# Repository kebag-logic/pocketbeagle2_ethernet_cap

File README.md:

# PocketBeagle 2 Ethernet Cap

Ethernet cap for the PocketBeagle 2, exposing the TSN features of the AM62x through a
DP83867IRPAPR gigabit PHY (RGMII), with full IO pass-through headers for stacking additional modules.

## Getting started

```sh
git clone <this repo>
git submodule update --init     # pulls kebag_logic_kicad_library
```

Open `pocketbeagle2_ethernet_cap.kicad_pro` with KiCad ≥ 9. All symbols/footprints
resolve project-locally through `sym-lib-table` / `fp-lib-table` into the
[kebag_logic_kicad_library](https://github.com/kebag-logic/kebag_logic_kicad_library)
submodule — no global library setup needed.

## Schematic structure

```
pocketbeagle2_ethernet_cap.kicad_sch   root: pure block diagram (sheet symbols only)
├── io.kicad_sch                       U1 PocketBeagle 2 + J2/J3 IO pass-through headers
├── network.kicad_sch                  network domain top
│   ├── phy.kicad_sch                  U2 DP83867 PHY, straps, decoupling, status LEDs
│   ├── rj45_connector_port0.kicad_sch J1 RJ45 magjack (integrated magnetics)
│   └── oscillator.kicad_sch           Y1 25 MHz HCMOS oscillator + clock conditioning
├── ldo_2v5.kicad_sch                  U4 TPS7A2025 -> VDD_2V5
└── ldo_1v1.kicad_sch                  U3 TPS7A2011 -> VDD_1V1
```

The design is fully hierarchical (shish-lan house style): **no global labels**. `GND`
is distributed via `power:GND` symbols; every other inter-sheet net crosses through
**hierarchical sheet-pin ports**, so signal flow is traceable through the hierarchy.
The root is a block diagram: `io` sources the RGMII/MDIO/reset/interrupt signals and
`VDD_3V3`, `network` consumes them, and the `ldo_*` sheets feed `VDD_2V5`/`VDD_1V1`.
Inside `io`, the PocketBeagle IOs fan out to the stacking headers as sheet-local nets;
only the 17 cap-used signals leave the sheet as ports.

## Documentation

- [documentation/connections.md](documentation/connections.md) — RGMII, MDI, MDIO,
  clocking, straps, audio, power tree, and the rev A → current net rename map
- [documentation/naming_convention.md](documentation/naming_convention.md) — mandatory
  signal naming rules
- [documentation/review_checklist.md](documentation/review_checklist.md) — everything
  awaiting user review after the restructure
- [documentation/library_additions.md](documentation/library_additions.md) — every
  part added to the KL library for this design (review checkpoint)
- [documentation/U2-DP83867IRPAPR_pin_out.md](documentation/U2-DP83867IRPAPR_pin_out.md)
- [documentation/current_consumption.md](documentation/current_consumption.md)

## Board state

**Rev B** (branch `revb-respin`) is manufactured and assembled by JLCPCB. All SMD parts are on the
top side; the RJ45 magjack J1 (TE 5-2301994-7, pin 1 left unsoldered) is hand-soldered on the bottom
and runs through the DP83867 RJ45 mirror mode. RGMII lengths are matched including the PocketBeagle 2
module side. Design and order details: [documentation/handover_revb_respin.md](documentation/handover_revb_respin.md).

Bring-up status (2026-10-07):

| Step | Result |
|------|--------|
| Visual inspection, rail-to-GND shorts | OK |
| Bench 3.3 V on P1.14, cape alone: VDD_2V5 / VDD_1V1 | OK |
| PocketBeagle 2 on USB-C, no SD card: rails | OK |
| Ethernet link LED on cable plug/unplug (PHY out of reset, auto-negotiation) | OK |
| Link speed on the switch side: 1000 Mb/s (all 4 pairs and mirror mode work) | OK |
| Linux: PHY detected over MDIO, 1000/Full, iperf3, RGMII delay tuning | to do (needs SD card) |

### Software

A Linux image for the PocketBeagle 2 with this cape is built from the
[ti-sitara-am65x-bsp](https://github.com/kebag-logic/ti-sitara-am65x-bsp). The device tree needs the PHY at `reg = <0>` and
`phy-mode = "rgmii-rxid"` (start with a 1.75 ns RX delay); see section 2.4 of the handover.

### Rev B pictures

Assembled board on the PocketBeagle 2:

Layout and 3D views:

### Rev A

The **rev A** routed board is preserved at git tag `revA-routed` (flight-time matching on the RGMII was
still open there).

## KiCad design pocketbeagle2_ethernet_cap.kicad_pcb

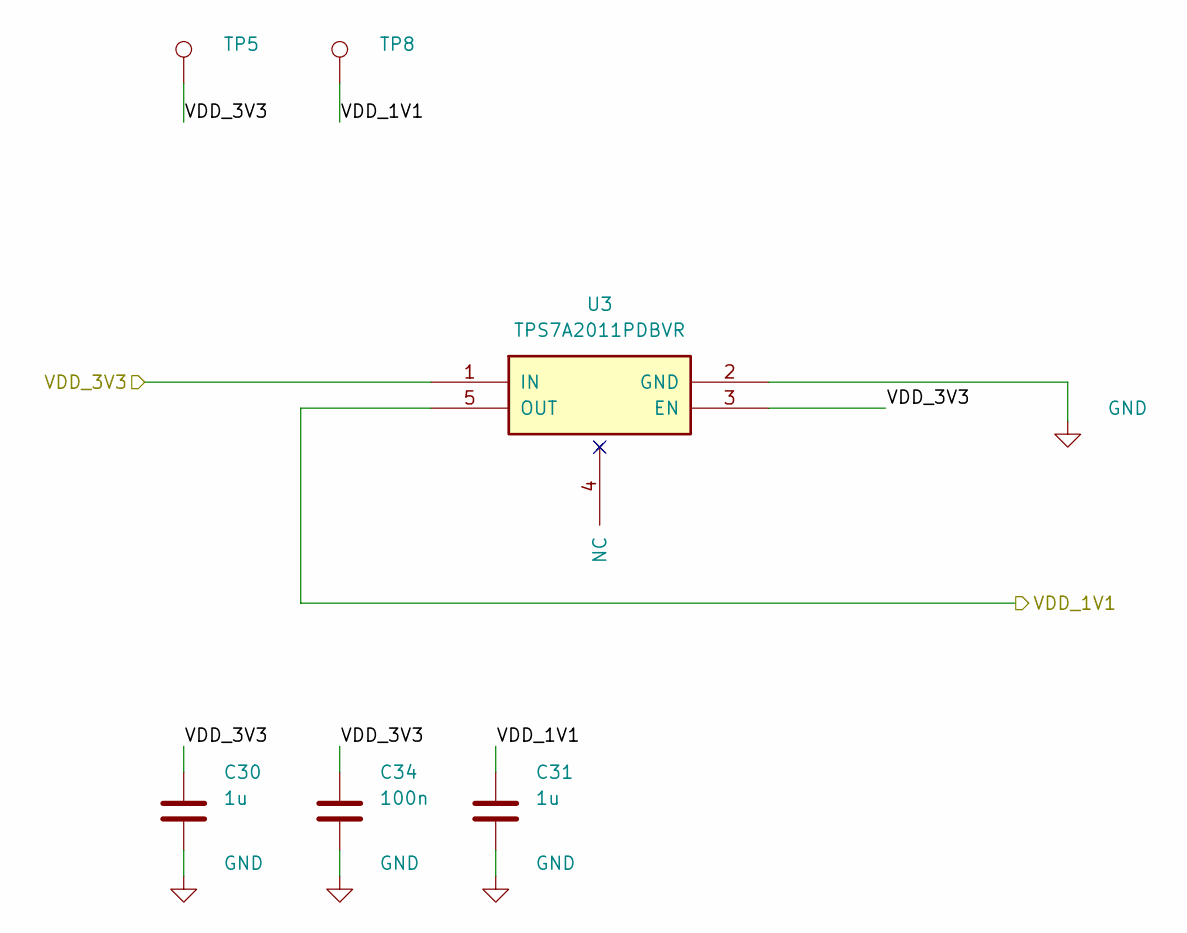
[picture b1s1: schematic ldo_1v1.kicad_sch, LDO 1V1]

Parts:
C30, C31: 1u; C_0402; Voltage_in_V 16; Tolerance_in_pct 10; MPN GRM155R61C105KA12D; Mouser 81-GRM155R61C105KA12D
C34: 100n; C_0402; Voltage_in_V 35; Tolerance_in_pct 10; MPN CGA2B3X7R1V104K050BB; Mouser 810-CGA2B3X7R1V104K
TP5, TP8: TestPoint_SMD; TestPoint_SMD_1.0x1.0mm
U3: TPS7A2011PDBVR; SOT-23-5; MPN TPS7A2011PDBVR; Mouser 595-TPS7A2011PDBVR

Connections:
/VDD_1V1: C31.1, TP8.1, U3.5 (OUT); also elsewhere on the board
/VDD_3V3: C30.1, C34.1, TP5.1, U3.1 (IN), U3.3 (EN); also elsewhere on the board
GND: C30.2, C31.2, C34.2, U3.2 (GND); also elsewhere on the board

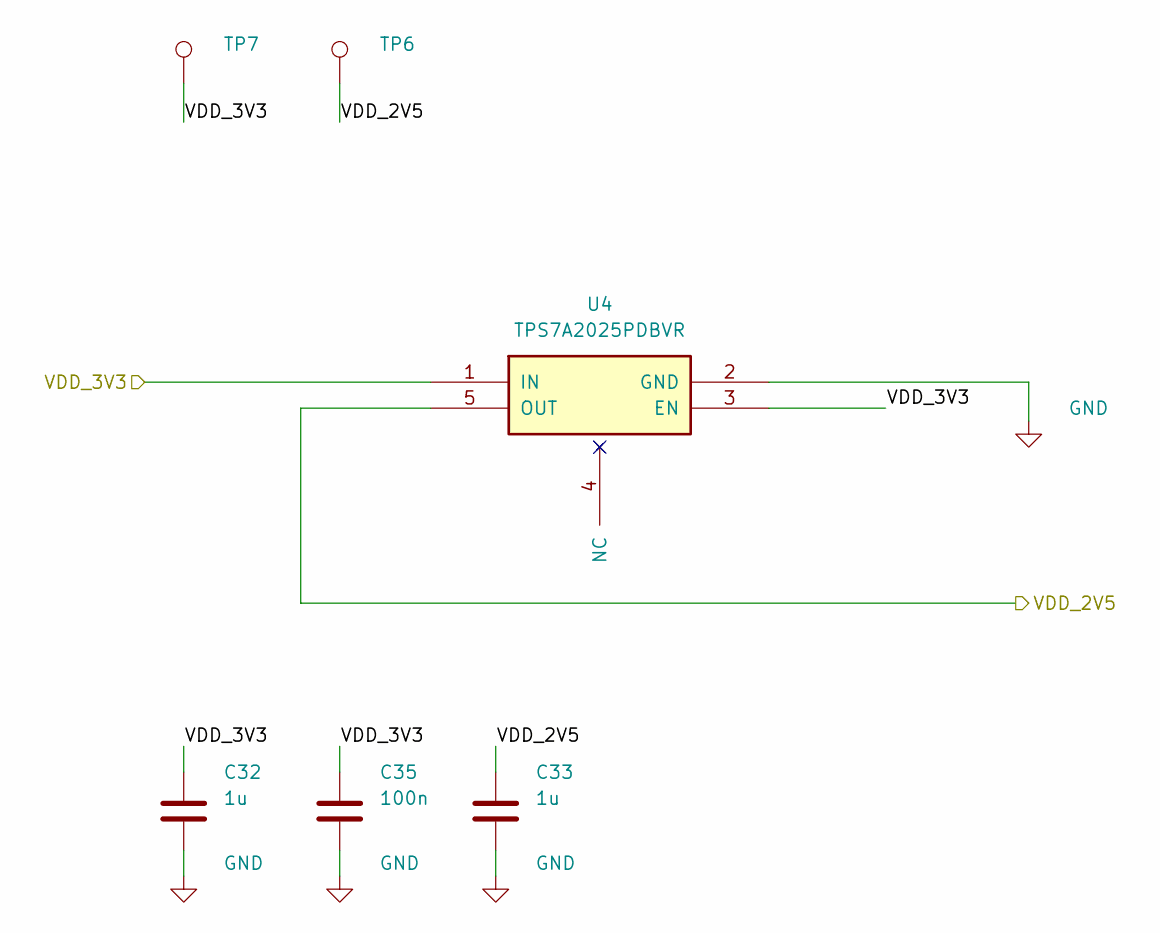
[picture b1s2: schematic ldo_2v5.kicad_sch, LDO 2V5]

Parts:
C32, C33: 1u; C_0402; Voltage_in_V 16; Tolerance_in_pct 10; MPN GRM155R61C105KA12D; Mouser 81-GRM155R61C105KA12D
C35: 100n; C_0402; Voltage_in_V 35; Tolerance_in_pct 10; MPN CGA2B3X7R1V104K050BB; Mouser 810-CGA2B3X7R1V104K
TP6, TP7: TestPoint_SMD; TestPoint_SMD_1.0x1.0mm
U4: TPS7A2025PDBVR; SOT-23-5; MPN TPS7A2025PDBVR; Mouser 595-TPS7A2025PDBVR

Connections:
/VDD_2V5: C33.1, TP6.1, U4.5 (OUT); also elsewhere on the board
/VDD_3V3: C32.1, C35.1, TP7.1, U4.1 (IN), U4.3 (EN); also elsewhere on the board
GND: C32.2, C33.2, C35.2, U4.2 (GND); also elsewhere on the board

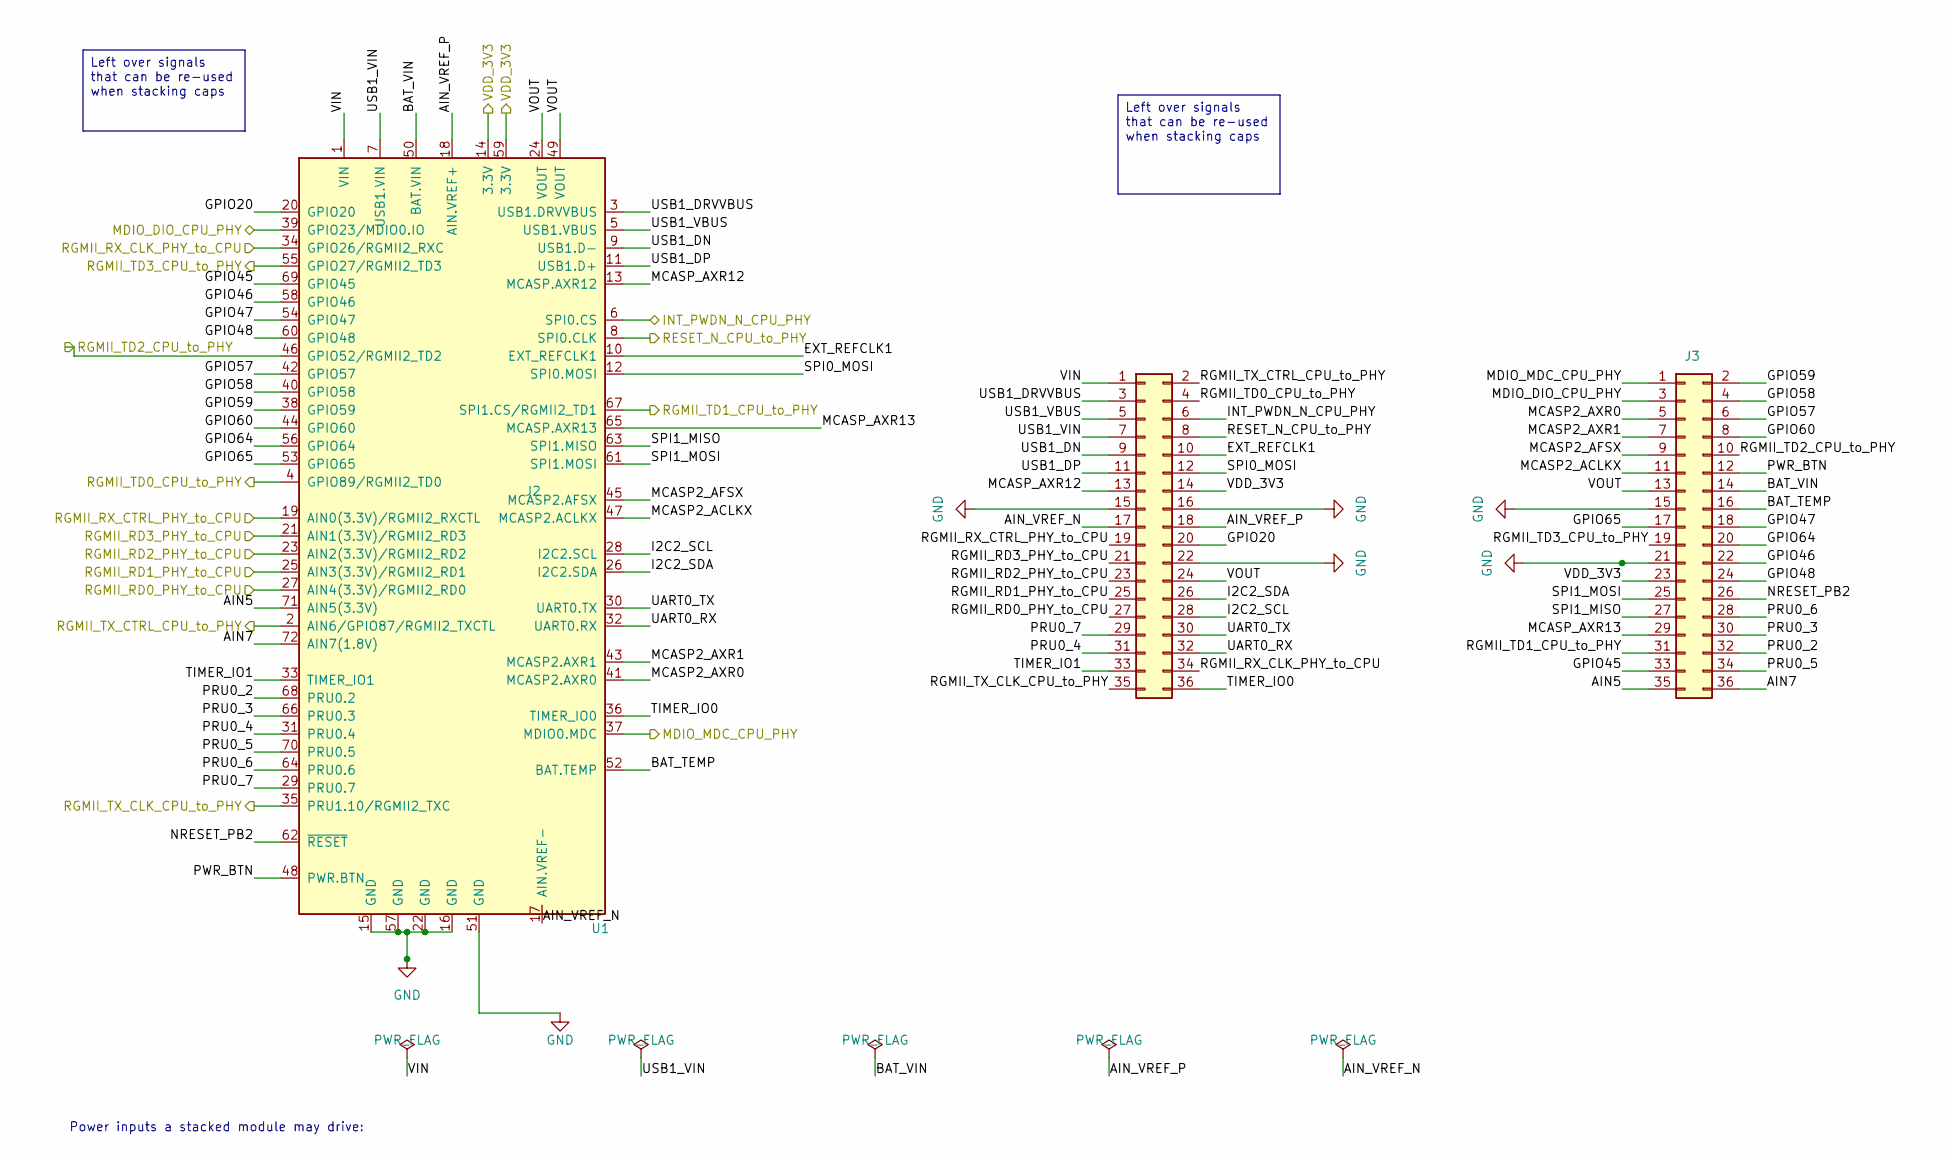
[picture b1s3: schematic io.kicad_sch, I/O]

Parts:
J2, J3: Header_18x02_2.54mm_2.54mm_Straight; 18x02_2.54mm_Header; MPN HC-PZ254-11.5L-2x18PZ; LCSC C41376109
U1: PocketBeagle2; BeagleBoard_PocketBeagle; MPN PocketBeagle 2; Mouser TBD

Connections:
/INT_PWDN_N_CPU_PHY: J2.6, U1.6 (SPI0.CS); also elsewhere on the board
/MDIO_DIO_CPU_PHY: J3.3, U1.39 (GPIO23/MDIO0.IO); also elsewhere on the board
/MDIO_MDC_CPU_PHY: J3.1, U1.37 (MDIO0.MDC); also elsewhere on the board
/RESET_N_CPU_to_PHY: J2.8, U1.8 (SPI0.CLK); also elsewhere on the board
/RGMII_RD0_PHY_to_CPU: J2.27, U1.27 (AIN4(3.3V)/RGMII2_RD0); also elsewhere on the board
/RGMII_RD1_PHY_to_CPU: J2.25, U1.25 (AIN3(3.3V)/RGMII2_RD1); also elsewhere on the board
/RGMII_RD2_PHY_to_CPU: J2.23, U1.23 (AIN2(3.3V)/RGMII2_RD2); also elsewhere on the board
/RGMII_RD3_PHY_to_CPU: J2.21, U1.21 (AIN1(3.3V)/RGMII2_RD3); also elsewhere on the board
/RGMII_RX_CLK_PHY_to_CPU: J2.34, U1.34 (GPIO26/RGMII2_RXC); also elsewhere on the board
/RGMII_RX_CTRL_PHY_to_CPU: J2.19, U1.19 (AIN0(3.3V)/RGMII2_RXCTL); also elsewhere on the board
/RGMII_TD0_CPU_to_PHY: J2.4, U1.4 (GPIO89/RGMII2_TD0); also elsewhere on the board
/RGMII_TD1_CPU_to_PHY: J3.31, U1.67 (SPI1.CS/RGMII2_TD1); also elsewhere on the board
/RGMII_TD2_CPU_to_PHY: J3.10, U1.46 (GPIO52/RGMII2_TD2); also elsewhere on the board
/RGMII_TD3_CPU_to_PHY: J3.19, U1.55 (GPIO27/RGMII2_TD3); also elsewhere on the board
/RGMII_TX_CLK_CPU_to_PHY: J2.35, U1.35 (PRU1.10/RGMII2_TXC); also elsewhere on the board
/RGMII_TX_CTRL_CPU_to_PHY: J2.2, U1.2 (AIN6/GPIO87/RGMII2_TXCTL); also elsewhere on the board
/VDD_3V3: J2.14, J3.23, U1.14 (3.3V), U1.59 (3.3V); also elsewhere on the board
/io/AIN5: J3.35, U1.71 (AIN5(3.3V))
/io/AIN7: J3.36, U1.72 (AIN7(1.8V))
/io/AIN_VREF_N: J2.17, U1.17 (AIN.VREF-)
/io/AIN_VREF_P: J2.18, U1.18 (AIN.VREF+)
/io/BAT_TEMP: J3.16, U1.52 (BAT.TEMP)
/io/BAT_VIN: J3.14, U1.50 (BAT.VIN)
/io/EXT_REFCLK1: J2.10, U1.10 (EXT_REFCLK1)
/io/GPIO20: J2.20, U1.20 (GPIO20)
/io/GPIO45: J3.33, U1.69 (GPIO45)
/io/GPIO46: J3.22, U1.58 (GPIO46)
/io/GPIO47: J3.18, U1.54 (GPIO47)
/io/GPIO48: J3.24, U1.60 (GPIO48)
/io/GPIO57: J3.6, U1.42 (GPIO57)
/io/GPIO58: J3.4, U1.40 (GPIO58)
/io/GPIO59: J3.2, U1.38 (GPIO59)
/io/GPIO60: J3.8, U1.44 (GPIO60)
/io/GPIO64: J3.20, U1.56 (GPIO64)
/io/GPIO65: J3.17, U1.53 (GPIO65)
/io/I2C2_SCL: J2.28, U1.28 (I2C2.SCL)
/io/I2C2_SDA: J2.26, U1.26 (I2C2.SDA)
/io/MCASP2_ACLKX: J3.11, U1.47 (MCASP2.ACLKX)
/io/MCASP2_AFSX: J3.9, U1.45 (MCASP2.AFSX)
/io/MCASP2_AXR0: J3.5, U1.41 (MCASP2.AXR0)
/io/MCASP2_AXR1: J3.7, U1.43 (MCASP2.AXR1)
/io/MCASP_AXR12: J2.13, U1.13 (MCASP.AXR12)
/io/MCASP_AXR13: J3.29, U1.65 (MCASP.AXR13)
/io/NRESET_PB2: J3.26, U1.62 (~RESET)
/io/PRU0_2: J3.32, U1.68 (PRU0.2)
/io/PRU0_3: J3.30, U1.66 (PRU0.3)
/io/PRU0_4: J2.31, U1.31 (PRU0.4)
/io/PRU0_5: J3.34, U1.70 (PRU0.5)
/io/PRU0_6: J3.28, U1.64 (PRU0.6)
/io/PRU0_7: J2.29, U1.29 (PRU0.7)
/io/PWR_BTN: J3.12, U1.48 (PWR.BTN)
/io/SPI0_MOSI: J2.12, U1.12 (SPI0.MOSI)
/io/SPI1_MISO: J3.27, U1.63 (SPI1.MISO)
/io/SPI1_MOSI: J3.25, U1.61 (SPI1.MOSI)
/io/TIMER_IO0: J2.36, U1.36 (TIMER_IO0)
/io/TIMER_IO1: J2.33, U1.33 (TIMER_IO1)
/io/UART0_RX: J2.32, U1.32 (UART0.RX)
/io/UART0_TX: J2.30, U1.30 (UART0.TX)
/io/USB1_DN: J2.9, U1.9 (USB1.D-)
/io/USB1_DP: J2.11, U1.11 (USB1.D+)
/io/USB1_DRVVBUS: J2.3, U1.3 (USB1.DRVVBUS)
/io/USB1_VBUS: J2.5, U1.5 (USB1.VBUS)
/io/USB1_VIN: J2.7, U1.7 (USB1.VIN)
/io/VIN: J2.1, U1.1 (VIN)
/io/VOUT: J2.24, J3.13, U1.24 (VOUT), U1.49 (VOUT)
GND: J2.15, J2.16, J2.22, J3.15, J3.21, U1.15 (GND), U1.16 (GND), U1.22 (GND), U1.51 (GND), U1.57 (GND); also elsewhere on the board

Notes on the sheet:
Power inputs a stacked module may drive:
Left over signals that can be re-used when stacking caps

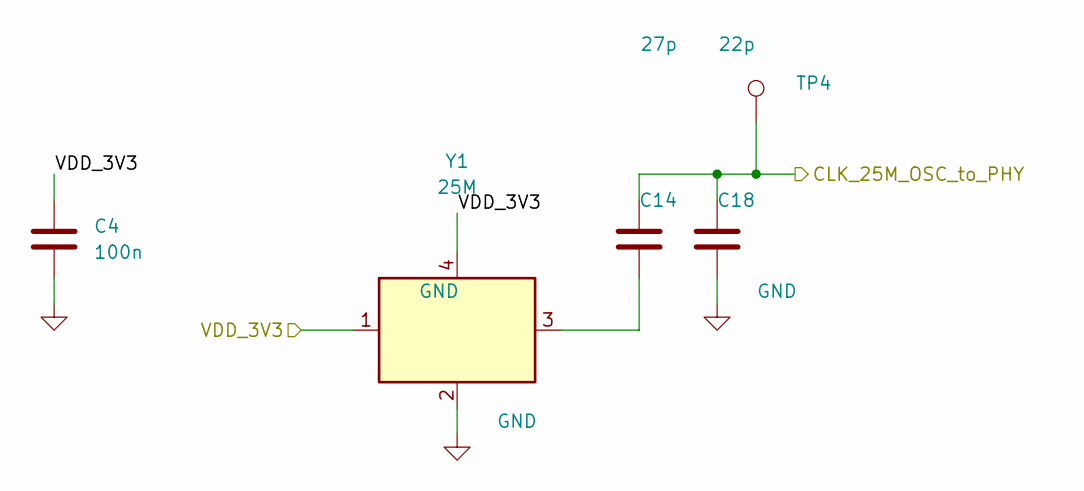
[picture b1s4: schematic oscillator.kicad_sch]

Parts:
C4: 100n; C_0402; Voltage_in_V 35; Tolerance_in_pct 10; MPN CGA2B3X7R1V104K050BB; Mouser 810-CGA2B3X7R1V104K
C14: 27p; C_0402; Voltage_in_V 50; Tolerance_in_pct 5; MPN GRM1555C1H270JA01D; Mouser 81-GRM1555C1H270JA01D
C18: 22p; C_0402; Voltage_in_V 50; Tolerance_in_pct 5; MPN GRM1555C1H220JA01D; Mouser 81-GRM1555C1H220JA01D
TP4: TestPoint_SMD; TestPoint_SMD_1.0x1.0mm
Y1: 25M; ECS-2520MV; Voltage_in_V 1.6-3.6; MPN ECS-2520MV-250-CN-TR; Mouser TBD

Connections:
/VDD_3V3: C4.1, Y1.1 (Tri-State), Y1.4 (VDD); also elsewhere on the board
/network/oscillator/CLK_25M_OSC_to_PHY: C14.2, C18.2, TP4.1; also elsewhere on the board
GND: C4.2, C18.1, Y1.2 (GND); also elsewhere on the board
unnamed: C14.1, Y1.3 (OUT)

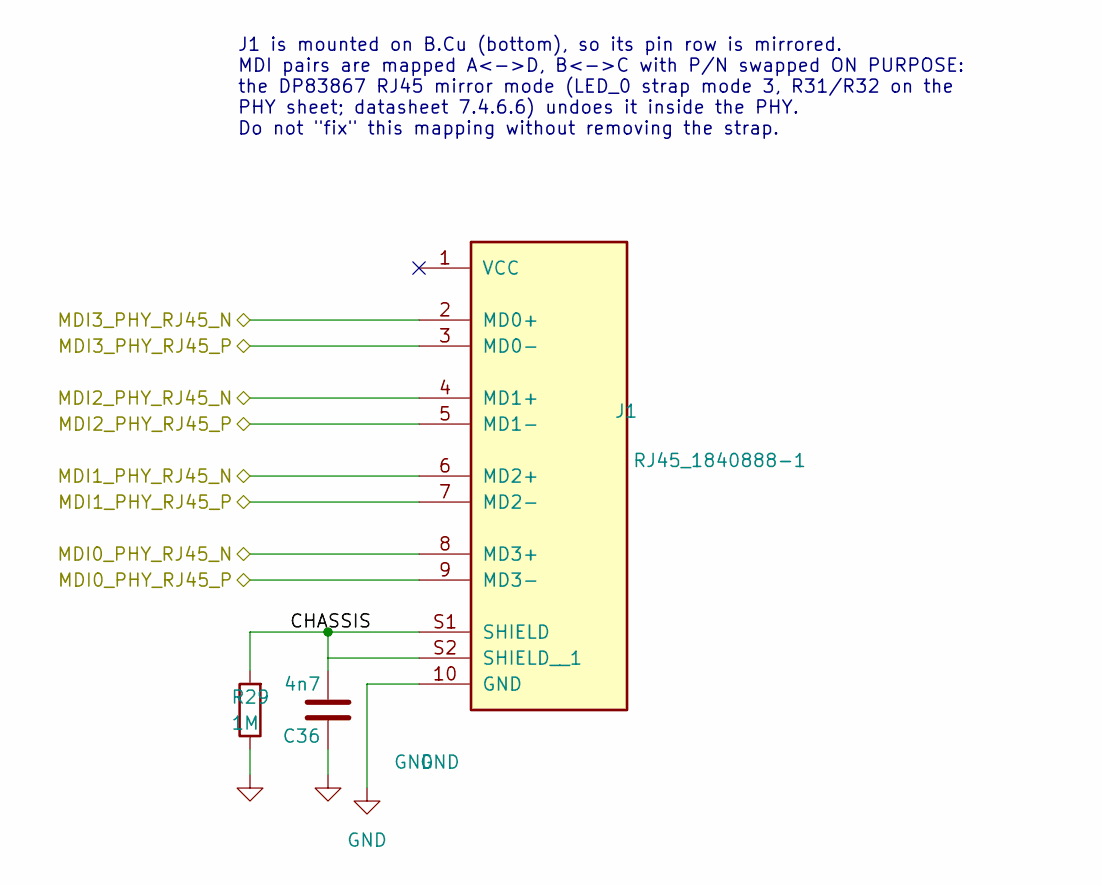
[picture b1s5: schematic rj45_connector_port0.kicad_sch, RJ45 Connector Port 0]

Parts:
C36: 4n7; C_1210; Tolerance_in_pct 10; Voltage_in_V 2000; MPN C1210C472KGRACTU
J1: RJ45_1840888-1; BEL_1840888-1; PARTREV 5; Mouser TBD
R29: 1M; R_1206; Tolerance_in_pct 1; MPN CRCW12061M00FKEA; LCSC C844869

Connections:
/network/phy/MDI0_PHY_RJ45_N: J1.8 (MD3+); also elsewhere on the board
/network/phy/MDI0_PHY_RJ45_P: J1.9 (MD3-); also elsewhere on the board
/network/phy/MDI1_PHY_RJ45_N: J1.6 (MD2+); also elsewhere on the board
/network/phy/MDI1_PHY_RJ45_P: J1.7 (MD2-); also elsewhere on the board
/network/phy/MDI2_PHY_RJ45_N: J1.4 (MD1+); also elsewhere on the board
/network/phy/MDI2_PHY_RJ45_P: J1.5 (MD1-); also elsewhere on the board
/network/phy/MDI3_PHY_RJ45_N: J1.2 (MD0+); also elsewhere on the board
/network/phy/MDI3_PHY_RJ45_P: J1.3 (MD0-); also elsewhere on the board
/network/rj45_connector_port0/CHASSIS: C36.2, J1.S1 (SHIELD), J1.S2 (SHIELD__1), R29.2
GND: C36.1, J1.10 (GND), R29.1; also elsewhere on the board

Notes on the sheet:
J1 is mounted on B.Cu (bottom), so its pin row is mirrored. MDI pairs are mapped A<->D, B<->C with P/N swapped ON PURPOSE: the DP83867 RJ45 mirror mode (LED_0 strap mode 3, R31/R32 on the PHY sheet; datasheet 7.4.6.6) undoes it inside the PHY. Do not "fix" this mapping without removing the strap.

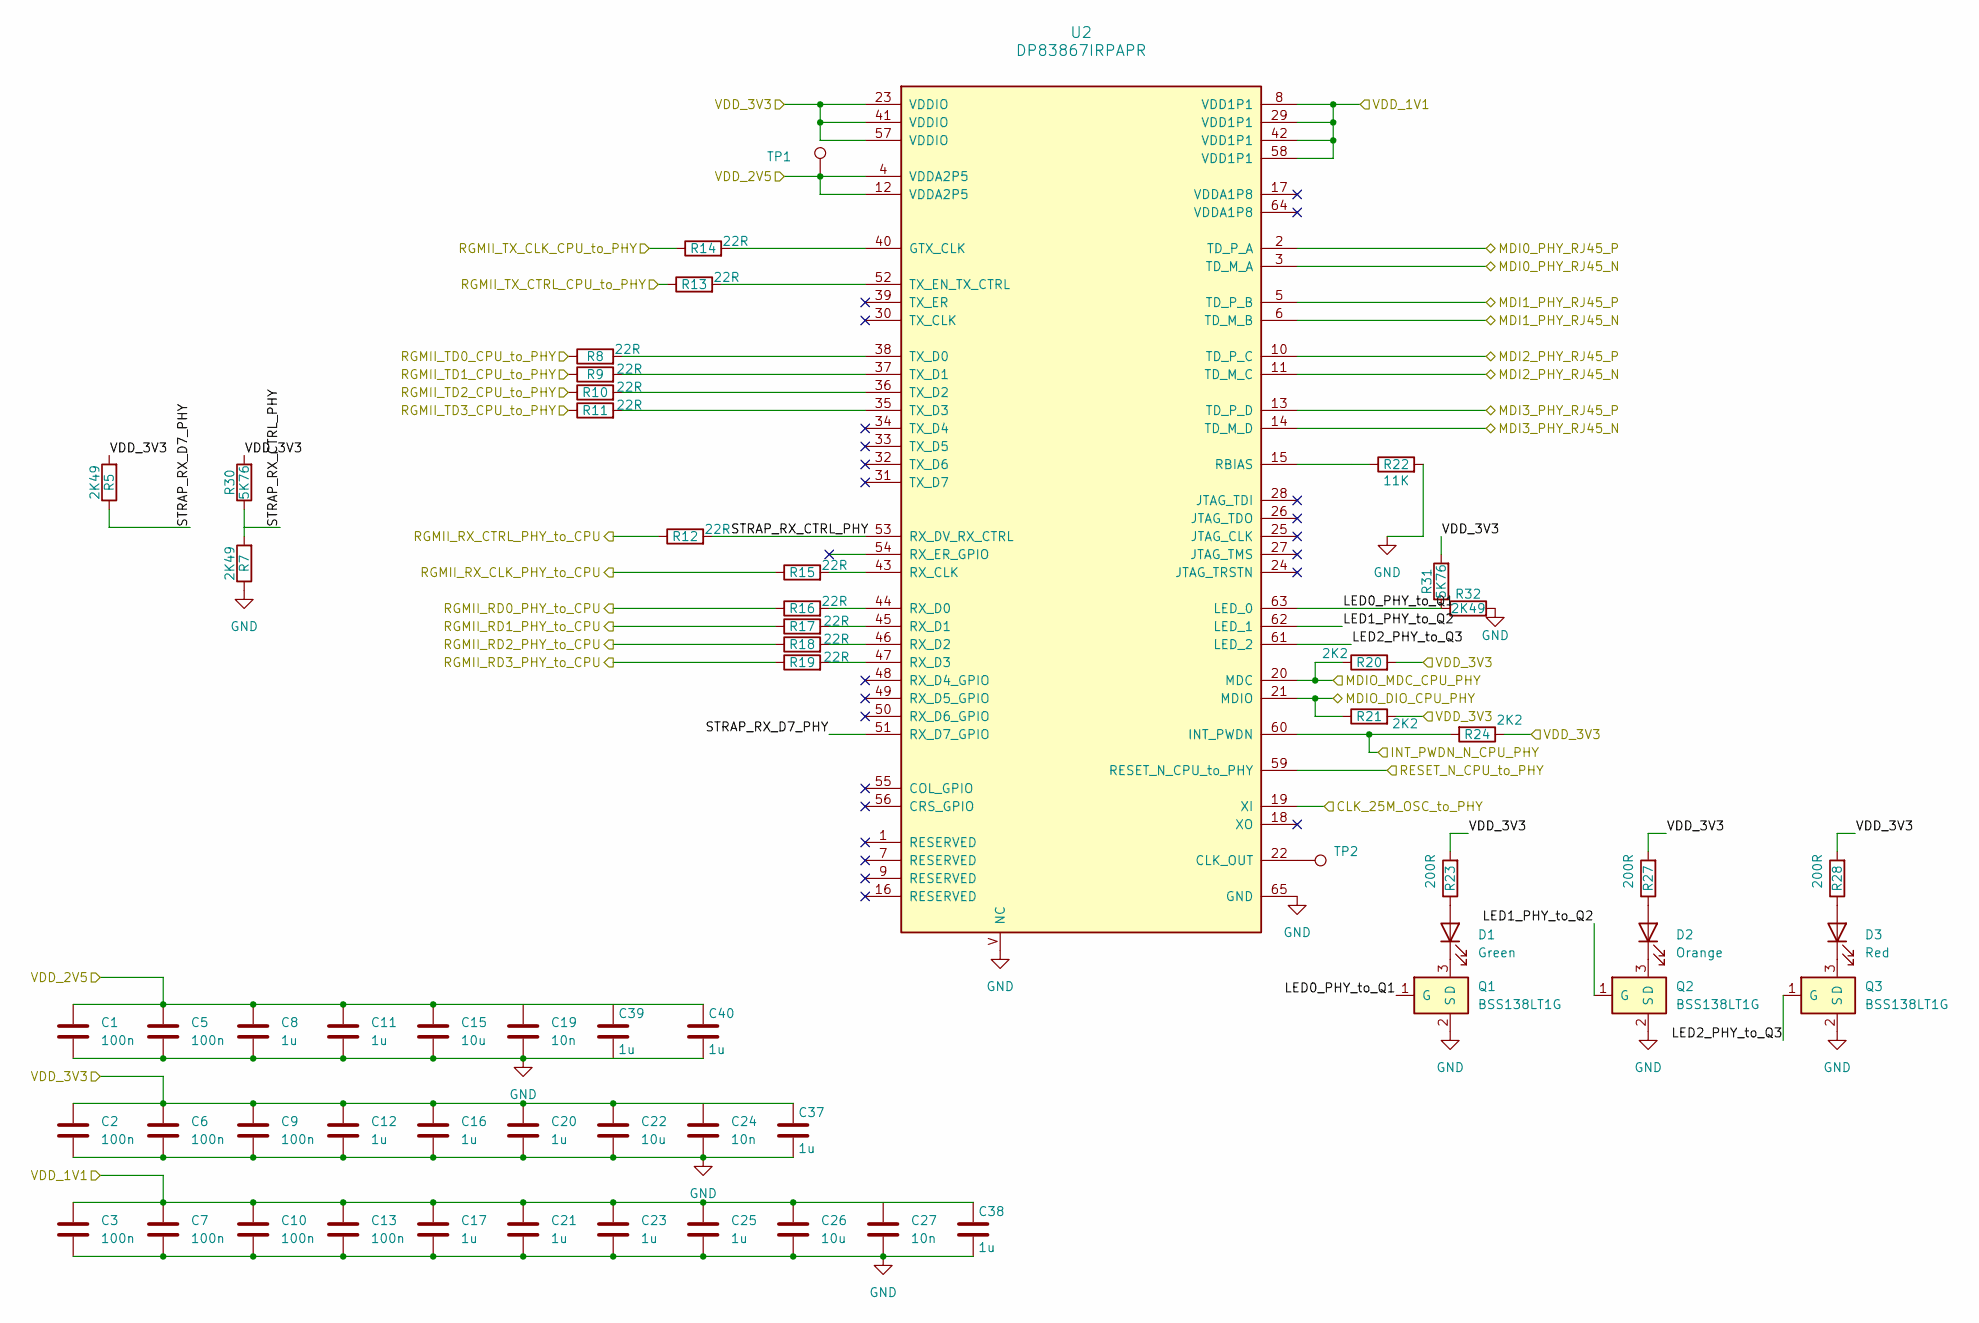
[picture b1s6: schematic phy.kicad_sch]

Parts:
C1, C2, C3, C5, C6, C7, C9, C10, C13: 100n; C_0402; Voltage_in_V 35; Tolerance_in_pct 10; MPN CGA2B3X7R1V104K050BB; Mouser 810-CGA2B3X7R1V104K
C8, C11, C12, C16, C17, C20, C21, C23, C25: 1u; C_0402; Voltage_in_V 16; Tolerance_in_pct 10; MPN GRM155R61C105KA12D; Mouser 81-GRM155R61C105KA12D
C15, C22, C26: 10u; C_0402; Voltage_in_V 6.3; Tolerance_in_pct 20; MPN GRM155R60J106ME44D; Mouser 81-GRM155R60J106ME44D
C19, C24, C27: 10n; C_0402; Voltage_in_V 50; Tolerance_in_pct 10; MPN GRM155R71H103KA88D; Mouser 81-GRM155R71H103KA88D
C37, C38, C39, C40: 1u; C_0402; Tolerance_in_pct 10; Voltage_in_V 16; MPN GRM155R61C105KA12D; Digikey 490-10694-1-ND
D1: Green; LED_0805; MPN LTST-C170GKT; Mouser 859-LTST-C170GKT
D2: Orange; LED_0805; MPN LTST-C170KFKT; Mouser 859-LTST-C170KFKT
D3: Red; LED_0805; MPN LTST-C170KRKT; Mouser 859-LTST-C170KRKT
Q1, Q2, Q3: BSS138LT1G; SOT-23; MPN BSS138LT1G; Mouser 863-BSS138LT1G
R5, R7: 2K49; R_0402; Tolerance_in_pct 1; MPN CRCW04022K49FKEDC; Mouser 71-CRCW04022K49FKEDC
R8, R9, R10, R11, R12, R13, R14, R15, R16, R17, R18, R19: 22R; R_0402; Tolerance_in_pct 1; MPN CRCW040222R0FKEDC; Mouser 71-CRCW040222R0FKEDC
R20, R21, R24: 2K2; R_0402; Tolerance_in_pct 1; MPN CRCW04022K20FKEDC; Mouser 71-CRCW04022K20FKEDC
R22: 11K; R_0402; Tolerance_in_pct 1; MPN CRCW040211K0FKEDC; Mouser 71-CRCW040211K0FKEDC
R23, R27, R28: 200R; R_0402; Tolerance_in_pct 1; MPN CRCW0402200RFKEDC; Mouser 71-CRCW0402200RFKEDC
R30, R31: 5K76; R_0402; Tolerance_in_pct 1; MPN CRCW04025K76FKEDC; Digikey 541-5031-1-ND
R32: 2K49; R_0402; Tolerance_in_pct 1; MPN CRCW04022K49FKEDC; Digikey 541-4867-1-ND
TP1, TP2: TestPoint_SMD; TestPoint_SMD_1.0x1.0mm
U2: DP83867IRPAPR; HTQFP-64_10x10mm_P0.5mm; MPN DP83867IRPAPR; Mouser 595-DP83867IRPAPR

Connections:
/INT_PWDN_N_CPU_PHY: R24.2, U2.60 (INT_PWDN); also elsewhere on the board
/MDIO_DIO_CPU_PHY: R21.1, U2.21 (MDIO); also elsewhere on the board
/MDIO_MDC_CPU_PHY: R20.1, U2.20 (MDC); also elsewhere on the board
/RESET_N_CPU_to_PHY: U2.59 (RESET_N_CPU_to_PHY); also elsewhere on the board
/RGMII_RD0_PHY_to_CPU: R16.1; also elsewhere on the board
/RGMII_RD1_PHY_to_CPU: R17.1; also elsewhere on the board
/RGMII_RD2_PHY_to_CPU: R18.1; also elsewhere on the board
/RGMII_RD3_PHY_to_CPU: R19.1; also elsewhere on the board
/RGMII_RX_CLK_PHY_to_CPU: R15.1; also elsewhere on the board
/RGMII_RX_CTRL_PHY_to_CPU: R12.1; also elsewhere on the board
/RGMII_TD0_CPU_to_PHY: R8.1; also elsewhere on the board
/RGMII_TD1_CPU_to_PHY: R9.1; also elsewhere on the board
/RGMII_TD2_CPU_to_PHY: R10.1; also elsewhere on the board
/RGMII_TD3_CPU_to_PHY: R11.1; also elsewhere on the board
/RGMII_TX_CLK_CPU_to_PHY: R14.1; also elsewhere on the board
/RGMII_TX_CTRL_CPU_to_PHY: R13.1; also elsewhere on the board
/VDD_1V1: C3.1, C7.1, C10.1, C13.1, C17.1, C21.1, C23.1, C25.1, C26.1, C27.1, C38.1, U2.8 (VDD1P1), U2.29 (VDD1P1), U2.42 (VDD1P1), U2.58 (VDD1P1); also elsewhere on the board
/VDD_2V5: C1.1, C5.1, C8.1, C11.1, C15.1, C19.1, C39.1, C40.1, TP1.1, U2.4 (VDDA2P5), U2.12 (VDDA2P5); also elsewhere on the board
/VDD_3V3: C2.1, C6.1, C9.1, C12.1, C16.1, C20.1, C22.1, C24.1, C37.1, R5.2, R20.2, R21.2, R23.2, R24.1, R27.2, R28.2, R30.2, R31.2, U2.23 (VDDIO), U2.41 (VDDIO), U2.57 (VDDIO); also elsewhere on the board
/network/oscillator/CLK_25M_OSC_to_PHY: U2.19 (XI); also elsewhere on the board
/network/phy/LED0_PHY_to_Q1: Q1.1 (G), R31.1, R32.1, U2.63 (LED_0)
/network/phy/LED1_PHY_to_Q2: Q2.1 (G), U2.62 (LED_1)
/network/phy/LED2_PHY_to_Q3: Q3.1 (G), U2.61 (LED_2)
/network/phy/MDI0_PHY_RJ45_N: U2.3 (TD_M_A); also elsewhere on the board
/network/phy/MDI0_PHY_RJ45_P: U2.2 (TD_P_A); also elsewhere on the board
/network/phy/MDI1_PHY_RJ45_N: U2.6 (TD_M_B); also elsewhere on the board
/network/phy/MDI1_PHY_RJ45_P: U2.5 (TD_P_B); also elsewhere on the board
/network/phy/MDI2_PHY_RJ45_N: U2.11 (TD_M_C); also elsewhere on the board
/network/phy/MDI2_PHY_RJ45_P: U2.10 (TD_P_C); also elsewhere on the board
/network/phy/MDI3_PHY_RJ45_N: U2.14 (TD_M_D); also elsewhere on the board
/network/phy/MDI3_PHY_RJ45_P: U2.13 (TD_P_D); also elsewhere on the board
/network/phy/STRAP_RX_CTRL_PHY: R7.2, R12.2, R30.1, U2.53 (RX_DV_RX_CTRL)
/network/phy/STRAP_RX_D7_PHY: R5.1, U2.51 (RX_D7_GPIO)
GND: C1.2, C2.2, C3.2, C5.2, C6.2, C7.2, C8.2, C9.2, C10.2, C11.2, C12.2, C13.2, C15.2, C16.2, C17.2, C19.2, C20.2, C21.2, C22.2, C23.2, C24.2, C25.2, C26.2, C27.2, C37.2, C38.2, C39.2, C40.2, Q1.2 (S), Q2.2 (S), Q3.2 (S), R7.1, R22.2, R32.2, U2.65 (GND), U2.V (NC); also elsewhere on the board
unnamed: D1.2 (A), R23.1
unnamed: D1.1 (K), Q1.3 (D)
unnamed: D2.2 (A), R27.1
unnamed: D2.1 (K), Q2.3 (D)
unnamed: D3.2 (A), R28.1
unnamed: D3.1 (K), Q3.3 (D)
unnamed: TP2.1, U2.22 (CLK_OUT)
unnamed: R14.2, U2.40 (GTX_CLK)
unnamed: R22.1, U2.15 (RBIAS)
unnamed: R15.2, U2.43 (RX_CLK)
unnamed: R16.2, U2.44 (RX_D0)
unnamed: R17.2, U2.45 (RX_D1)
unnamed: R18.2, U2.46 (RX_D2)
unnamed: R19.2, U2.47 (RX_D3)
unnamed: R8.2, U2.38 (TX_D0)
unnamed: R9.2, U2.37 (TX_D1)
unnamed: R10.2, U2.36 (TX_D2)
unnamed: R11.2, U2.35 (TX_D3)
unnamed: R13.2, U2.52 (TX_EN_TX_CTRL)

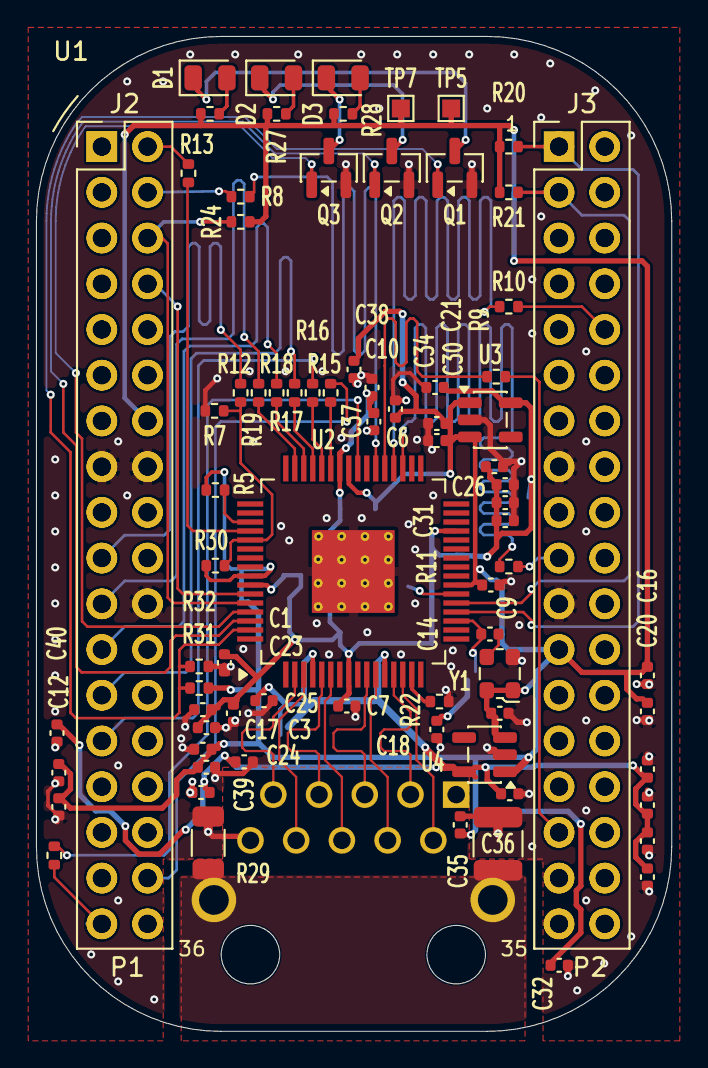
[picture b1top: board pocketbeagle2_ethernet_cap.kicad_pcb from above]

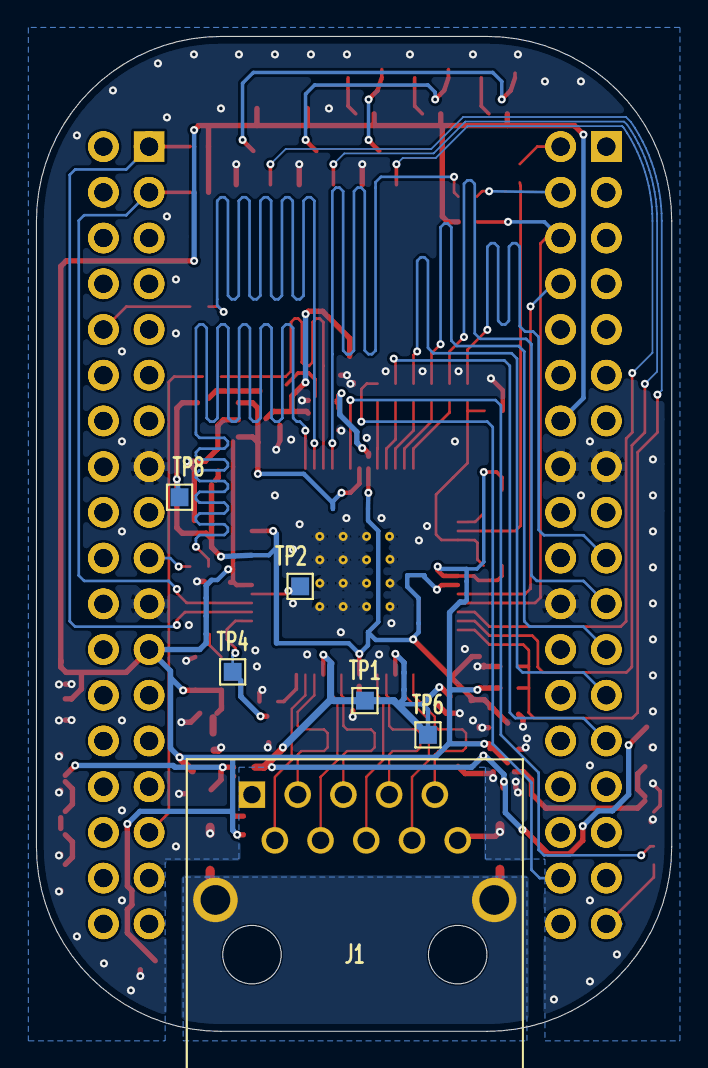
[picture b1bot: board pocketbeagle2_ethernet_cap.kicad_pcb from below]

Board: 4 copper layers, 35.3 x 55.3 mm, 84 parts (6 on the bottom side), 103 nets.

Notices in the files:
io.kicad_sch:
This source describes Open Hardware and is licensed under the
CERN-OHL-S v2.0.
using it under the terms of the CERN-OHL-S v2.0 (https://cern.ch/ohl).
